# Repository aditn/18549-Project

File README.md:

# PSTR - posture
Project website:
<a href="https://www.ece.cmu.edu/~ece549/spring17/team15/website/"> PSTR official website </a>
Project video link:
N/A (working on it now)

### This is a CMU 18549 project done by Team 15 with the following Team members:
 -  Benson Zhang (yaxiangz)

 - Adit Namdev (anamdev)

 - Tony Jin (tdjin)

 - Nikhil Nilakantan (nnilakan)

## System components

1. Hardware
    > Maintainers: Adit & Nikil

2. Software
    > Maintainers: Benson & Tony

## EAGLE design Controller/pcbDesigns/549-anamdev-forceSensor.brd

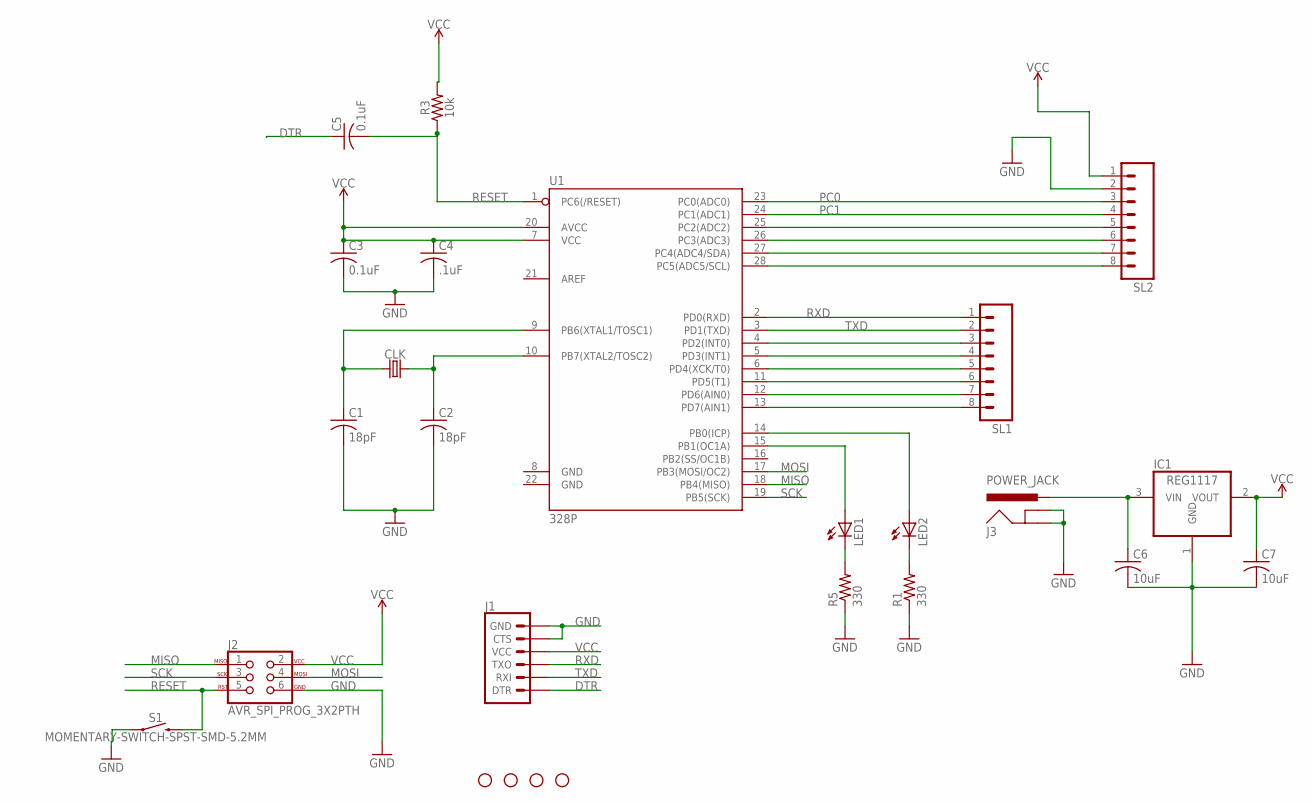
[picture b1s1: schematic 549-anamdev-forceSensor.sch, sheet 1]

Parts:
C1, C2: 18pF; C1206
C3, C5: 0.1uF; C1206
C4: .1uF; C1206
C6, C7: 10uF; C1206
CLK: CRYSTALSMD-HC49UP; HC49UP
H1, H2, H3, H4: STAND-OFF
IC1: REG1117; SOT223
J1: 6_PIN_SERIAL_TARGET; 1X06
J2: AVR_SPI_PROG_3X2PTH; 2X3
J3: POWER_JACK; POWER_JACK_PTH
LED1, LED2: LED1206; LED-1206
R1, R5: 330; R1206
R3: 10k; 1206
S1: MOMENTARY-SWITCH-SPST-SMD-5.2MM; TACTILE_SWITCH_SMD_5.2MM
SL1, SL2: M08; 08P
U1: 328P; DIP28

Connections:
DTR: C5.1, J1.1 (DTR)
GND: C1.2, C2.2, C3.2, C4.2, C6.2, C7.2, IC1.1 (GND), J1.5 (CTS), J1.6 (GND), J2.6, J3.GND, J3.GNDBREAK, R1.1, R5.1, S1.1, SL2.2; also elsewhere on the board
MISO: J2.1, U1.18 (PB4(MISO))
MOSI: J2.4, U1.17 (PB3(MOSI/OC2))
unnamed: LED2.A, U1.14 (PB0(ICP))
unnamed: LED1.C, R5.2
unnamed: LED1.A, U1.15 (PB1(OC1A))
unnamed: LED2.C, R1.2
unnamed: C6.1, IC1.3 (VIN), J3.PWR
unnamed: SL2.6, U1.26 (PC3(ADC3))
unnamed: SL1.5, U1.6 (PD4(XCK/T0))
unnamed: SL1.6, U1.11 (PD5(T1))
unnamed: SL1.7, U1.12 (PD6(AIN0))
unnamed: SL1.8, U1.13 (PD7(AIN1))
unnamed: SL1.3, U1.4 (PD2(INT0))
unnamed: SL1.4, U1.5 (PD3(INT1))
unnamed: C1.1, CLK.1, U1.9 (PB6(XTAL1/TOSC1))
unnamed: C2.1, CLK.2, U1.10 (PB7(XTAL2/TOSC2))
PC0: SL2.3, U1.23 (PC0(ADC0)); also elsewhere on the board
PC1: SL2.4, U1.24 (PC1(ADC1)); also elsewhere on the board
PC2: SL2.5, U1.25 (PC2(ADC2))
RESET: C5.2, J2.5, R3.1, S1.3 (2), U1.1 (PC6(/RESET))
RXD: J1.3 (TXO), SL1.1, U1.2 (PD0(RXD))
SCK: J2.3, U1.19 (PB5(SCK)); also elsewhere on the board
SCL: SL2.8, U1.28 (PC5(ADC5/SCL))
SDA: SL2.7, U1.27 (PC4(ADC4/SDA))
TXD: J1.2 (RXI), SL1.2, U1.3 (PD1(TXD))
VCC: C3.1, C4.1, C7.1, IC1.2 (VOUT), J1.4 (VCC), J2.2, R3.2, SL2.1, U1.7 (VCC), U1.20 (AVCC); also elsewhere on the board

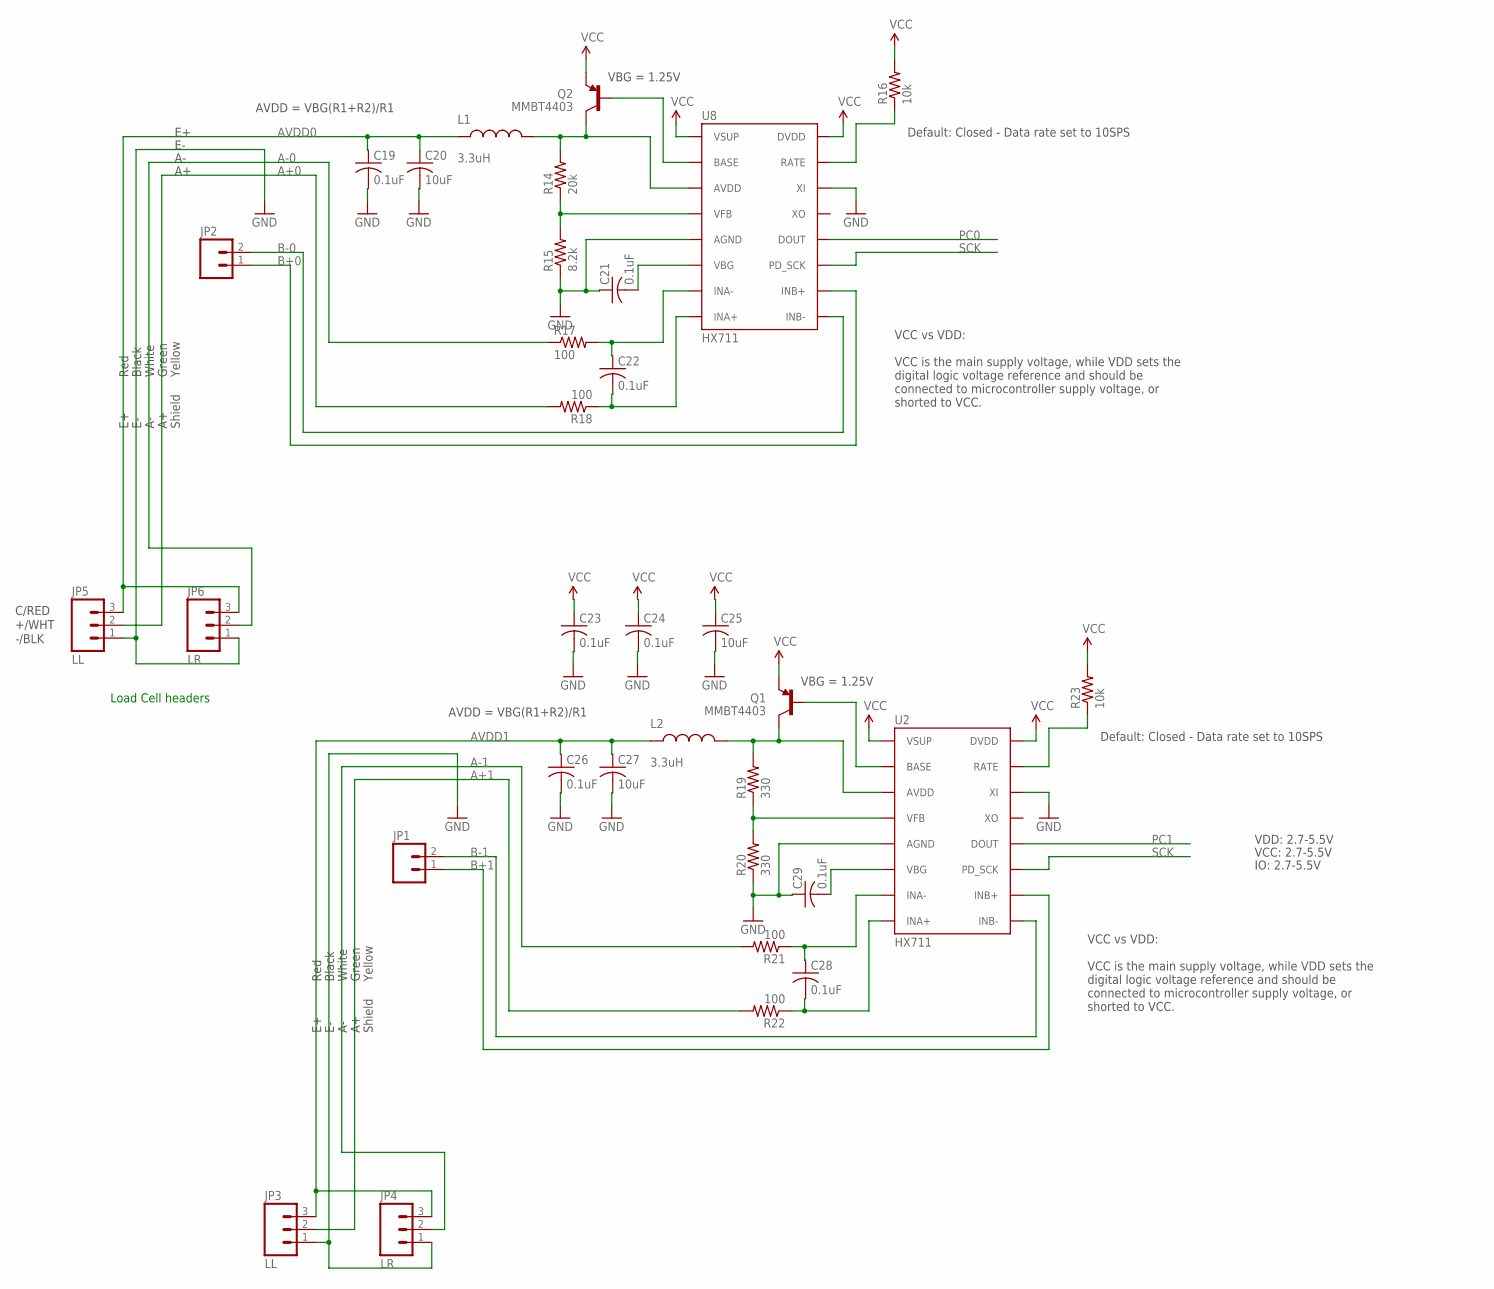
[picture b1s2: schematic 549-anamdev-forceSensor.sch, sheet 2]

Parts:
C19, C21, C22, C23, C24, C26, C28, C29: 0.1uF; C1206
C20, C25, C27: 10uF; C1206
JP1, JP2: M02PTH; 1X02
JP3, JP5: LL; 1X03
JP4, JP6: LR; 1X03
L1, L2: 3.3uH; 0805
Q1, Q2: MMBT4403; SOT23-3
R14: 20k; R1206
R15: 8.2k; R1206
R16, R23: 10k; R1206
R17, R18, R21, R22: 100; R1206
R19, R20: 330; R1206
U2, U8: HX711; SO16

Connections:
A+0: JP5.2, R18.2
A+1: JP3.2, R22.2
A-0: JP6.2, R17.1
A-1: JP4.2, R21.2
AVDD0: C19.1, C20.1, JP5.3, JP6.3, L1.1
AVDD1: C26.1, C27.1, JP3.3, JP4.3, L2.1
B+0: JP2.1, U8.10 (INB+)
B+1: JP1.1, U2.10 (INB+)
B-0: JP2.2, U8.9 (INB-)
B-1: JP1.2, U2.9 (INB-)
GND: C19.2, C20.2, C21.1, C23.2, C24.2, C25.2, C26.2, C27.2, C29.1, JP3.1, JP4.1, JP5.1, JP6.1, R15.1, R20.1, U2.5 (AGND), U2.14 (XI), U8.5 (AGND), U8.14 (XI); also elsewhere on the board
unnamed: Q2.1 (B), U8.2 (BASE)
unnamed: R14.1, R15.2, U8.4 (VFB)
unnamed: C21.2, U8.6 (VBG)
unnamed: L1.2, Q2.3 (C), R14.2, U8.3 (AVDD)
unnamed: R16.1, U8.15 (RATE)
unnamed: C22.1, R17.2, U8.7 (INA-)
unnamed: C22.2, R18.1, U8.8 (INA+)
unnamed: Q1.1 (B), U2.2 (BASE)
unnamed: R19.1, R20.2, U2.4 (VFB)
unnamed: C29.2, U2.6 (VBG)
unnamed: L2.2, Q1.3 (C), R19.2, U2.3 (AVDD)
unnamed: R23.1, U2.15 (RATE)
unnamed: C28.1, R21.1, U2.7 (INA-)
unnamed: C28.2, R22.1, U2.8 (INA+)
PC0: U8.12 (DOUT); also elsewhere on the board
PC1: U2.12 (DOUT); also elsewhere on the board
SCK: U2.11 (PD_SCK), U8.11 (PD_SCK); also elsewhere on the board
VCC: C23.1, C24.1, C25.1, Q1.2 (E), Q2.2 (E), R16.2, R23.2, U2.1 (VSUP), U2.16 (DVDD), U8.1 (VSUP), U8.16 (DVDD); also elsewhere on the board

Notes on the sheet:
VBG = 1.25V
AVDD = VBG(R1+R2)/R1
Default: Closed - Data rate set to 10SPS
VCC vs VDD: VCC is the main supply voltage, while VDD sets the digital logic voltage reference and should be connected to microcontroller supply voltage, or shorted to VCC.
Red
Black
White
Green
-/BLK
+/WHT
C/RED
Shield
Yellow
Load Cell headers
VCC: 2.7-5.5V
IO: 2.7-5.5V
VDD: 2.7-5.5V

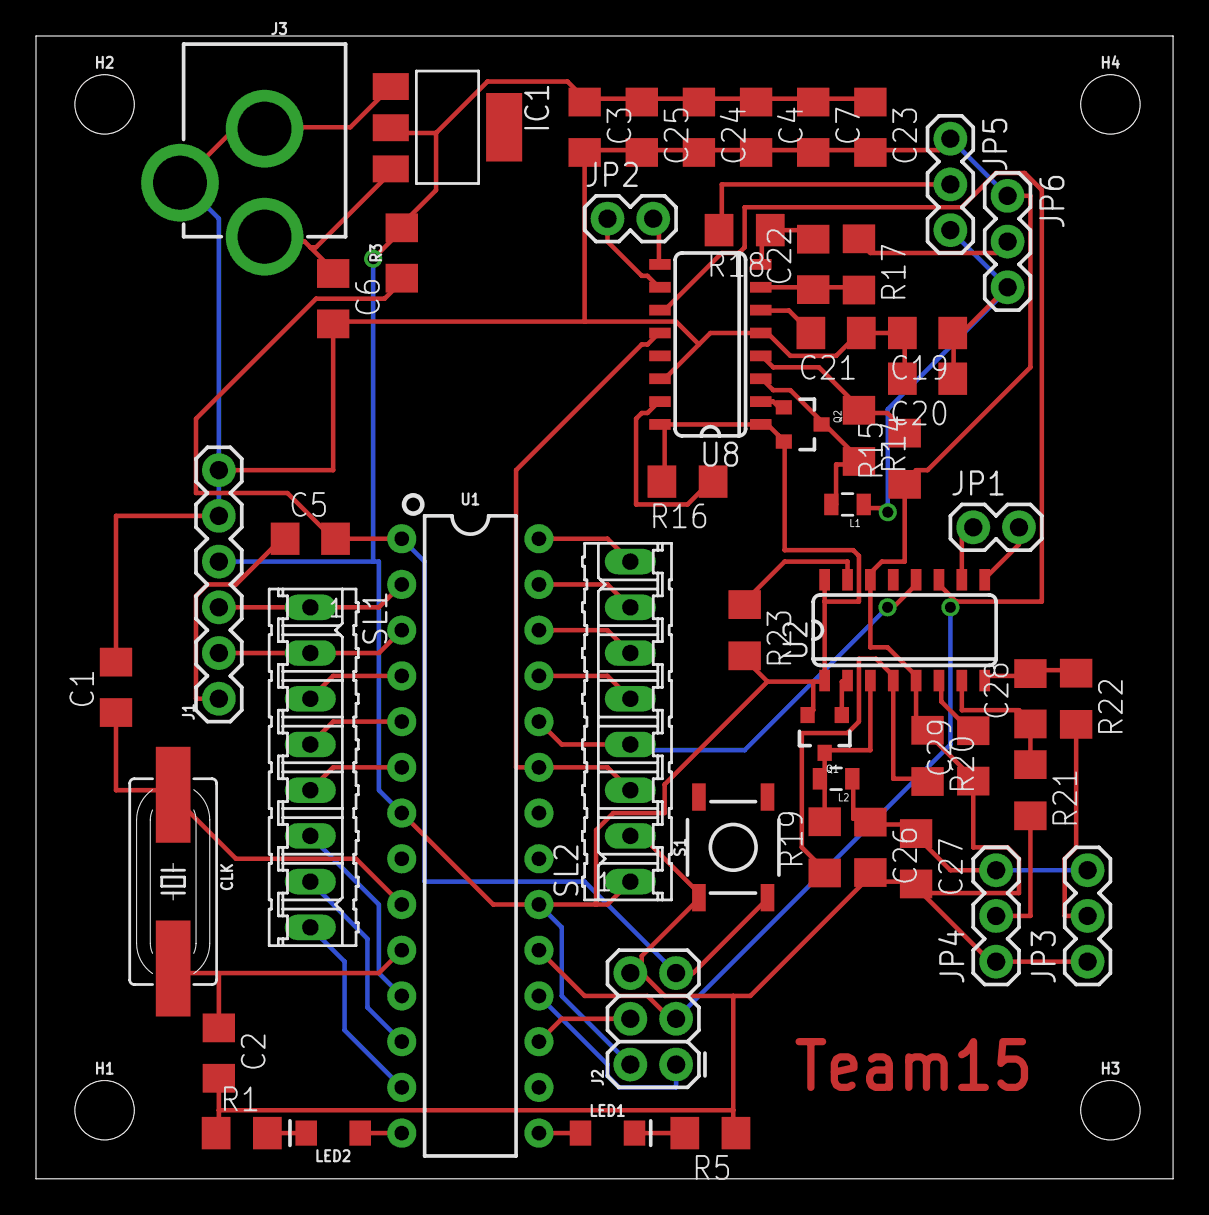
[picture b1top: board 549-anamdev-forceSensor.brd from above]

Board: 2 copper layers, 63.2 x 63.5 mm, 58 parts (0 on the bottom side), 52 nets.

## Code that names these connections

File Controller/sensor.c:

/*
  sensor.c
*/

#include "sensor.h"
#include <avr/interrupt.h>
#include <stdio.h>


void sensor_init(){

  /************ LOAD CELL MCU **************/
  //DDRC |= (1<<PC0); // Set PC0(clk) as an output pin
  //DDRC &= ~(1<<PC1); // Set PC1(data) as input pin

  //SENSORS[SENSOR0].CLK = PC0;
  //SENSORS[SENSOR0].DATA = PC1;
  //SENSORS[SENSOR0].DIR_REG = &DDRC;
  //SENSORS[SENSOR0].PORT_OUTPUT_REG = &PORTC;
  //SENSORS[SENSOR0].PORT_INPUT_REG = &PINC;
  //SENSORS[SENSOR0].CALIB_FACTOR = -12000;

  /* Initializing second sensor */
  //DDRC |= (1<<PC2); // Set P(clk) as an output pin
  //DDRC &= ~(1<<PC3); // Set PC3(data) as input pin

  //SENSORS[SENSOR1].CLK = PC2;
  //SENSORS[SENSOR1].DATA = PC3;
  //SENSORS[SENSOR1].DIR_REG = &DDRC;
  //SENSORS[SENSOR1].PORT_OUTPUT_REG = &PORTC;
  //SENSORS[SENSOR1].PORT_INPUT_REG = &PINC;
  //SENSORS[SENSOR1].CALIB_FACTOR = -11000;
  /* Initializing second sensor */


  /* Initializing THIRD PORTD sensor */
  //DDRD |= (1<<PD7); // Set PD7(clk) as an output pin
  //DDRD &= ~(1<<PD6); // Set PD6(data) as input pin

  //SENSORS[SENSOR2].CLK = PD7;
  //SENSORS[SENSOR2].DATA = PD6;
  //SENSORS[SENSOR2].DIR_REG = &DDRD;
  //SENSORS[SENSOR2].PORT_OUTPUT_REG = &PORTD;
  //SENSORS[SENSOR2].PORT_INPUT_REG = &PIND;
  //SENSORS[SENSOR2].CALIB_FACTOR = -11000;
  /* Initializing THIRD PORTD sensor */

  /* Initializing FOURTH PORTB sensor */
  //DDRB |= (1<<PB5); // Set PB5(clk) as an output pin
  //DDRB &= ~(1<<PB4); // Set PB4(data) as input pin

  //SENSORS[SENSOR3].CLK = PB5;
  //SENSORS[SENSOR3].DATA = PB4;
  //SENSORS[SENSOR3].DIR_REG = &DDRB;
  //SENSORS[SENSOR3].PORT_OUTPUT_REG = &PORTB;
  //SENSORS[SENSOR3].PORT_INPUT_REG = &PINB;
  //SENSORS[SENSOR3].CALIB_FACTOR = -11000;
  /* Initializing THIRD PORTD sensor */
  /************ LOAD CELL MCU **************/


  /**************** FSR MCU ****************/
  DDRC &= (~_BV(PC2) | ~_BV(PC1) | ~_BV(PC0)); // Set ADC pins PC(2-0) as input pins
  /**************** FSR MCU ****************/
}

uint16_t adc_read(uint8_t adcx) {
  /* adcx is the analog pin we want to use.  ADMUX's first few bits are
   * the binary representations of the numbers of the pins so we can
   * just 'OR' the pin's number with ADMUX to select that pin.
   * We first zero the four bits by setting ADMUX equal to its higher
   * four bits. */

  ADMUX &=  0xf0;
  ADMUX |=  adcx;

  /* This starts the conversion. */
  ADCSRA |= _BV(ADSC);

  /* This is an idle loop that just wait around until the conversion
   * is finished.  It constantly checks ADCSRA's ADSC bit, which we just
   * set above, to see if it is still set.  This bit is automatically
   * reset (zeroed) when the conversion is ready so if we do this in
   * a loop the loop will just go until the conversion is ready. */
  while (!( ADCSRA & _BV(ADIF)) );

  uint16_t adcV = ADC;
  ADCSRA |= _BV(ADIF);
  //printf("adcV:%d\n\r",adcV);


  /* Finally, we return the converted value to the calling function. */
  return adcV;
}

void adc_init(){
   // disable interrupts
   //cli();

   // Set the ADC prescaler to 128 (i.e., 16MHz/128 = 125KHz)
   ADCSRA |= ( 1 << ADPS2 ) | ( 1 << ADPS1 ) | ( 1 << ADPS0 );

   // Set the voltage reference from AVcc (i.e., 5V).
   ADMUX |= ( 1 << REFS0 );

   // Turn on the ADC.
   ADCSRA |= ( 1 << ADEN );

   // Do the initial conversion (i.e., the slowest conversion)
   // to ensure that everything is up and running.
   //ADCSRA |= ( 1 << ADSC );
  
   //enable interrupts
   //sei();
}

uint32_t read_avg_force(uint8_t sensor_id, uint8_t times){
  uint32_t avg=0;
  uint8_t i;
  for (i=0;i<times;i++){
     avg+=ReadCount(sensor_id);
  }
  avg/=times;
  return avg;
} 

void tare(){
  uint8_t sensor_id=0;

  for (sensor_id=0; sensor_id < NUMBER_OF_SENSORS; sensor_id++) {
    SENSORS[sensor_id].CALIB_OFFSET = 0;
    SENSORS[sensor_id].CALIB_OFFSET = read_avg_force(sensor_id, 15);
    printf("taring sensor%d:%lu\n\r",sensor_id, SENSORS[sensor_id].CALIB_OFFSET);
  }
}

float read_calibrated_value(uint8_t sensor_id){
  uint32_t avg;
  int32_t avg_offset;
 
  float calib_val=0;
  avg = read_avg_force(sensor_id, 2);
  avg_offset = ((int32_t)avg-SENSORS[sensor_id].CALIB_OFFSET);
  calib_val = (float)avg_offset/SENSORS[sensor_id].CALIB_FACTOR;
 
  return(calib_val);
}

uint32_t ReadCount(uint8_t sensor_id){
  uint32_t Count;
  uint8_t i;

  uint8_t clk = SENSORS[sensor_id].CLK;
  uint8_t data = SENSORS[sensor_id].DATA;
  volatile uint8_t *output_reg = SENSORS[sensor_id].PORT_OUTPUT_REG;
  volatile uint8_t *input_reg = SENSORS[sensor_id].PORT_INPUT_REG;

  *output_reg &= ~_BV(clk);
  *output_reg |= _BV(data);

  Count=0;

  while(*input_reg & _BV(data)); 
  for (i=0;i<24;i++){
    *output_reg |= _BV(clk);
    Count=Count<<1;
    *output_reg &= ~_BV(clk);
    if(*input_reg & _BV(data)) Count++;
  }
  
  *output_reg |= _BV(clk);
  Count=Count^0x800000;
  *output_reg &= ~_BV(clk);

  return(Count);
} 

void collectforceData(float* data){
  data[SENSOR0] = read_calibrated_value(SENSOR0);

  data[SENSOR1] = read_calibrated_value(SENSOR1);

  data[SENSOR2] = read_calibrated_value(SENSOR2);

  data[SENSOR3] = read_calibrated_value(SENSOR3);
}

void read_FSR(float* data) {
  data[SENSOR0] = adc_read(PC0);
  data[SENSOR1] = adc_read(PC1);
  data[SENSOR2] = adc_read(PC2);
}

void LED_green_on(){
  DDRC |= (1<<PC0);

  // set PC0 and PC1 to logic 1
  PORTC |= (1<<PC0);
}
void LED_green_off(){
  PORTC &= ~(1<<PC0);
}
void LED_red_on(){
  DDRC |= (1<<PC1);

  // set PC1 to logic 1
  PORTC |= (1<<PC1);
}
void LED_red_off(){
  PORTC &= ~(1<<PC1);
}

void LED_both_on(){
  // set Pins PC0,PC1 as outputs
  //DDRC = 0;
  DDRC |= (1<<PC0) | (1<<PC1);

  // set PC0 and PC1 to logic 1
  PORTC |= (1<<PC0) | (1<<PC1);
}

void LED_both_off(){
  // set Pins PC0,PC1 as outputs
  //DDRC = 0;
  //DDRC |= (1<<PC0) | (1<<PC1);

  // set PC0 and PC1 to logic 1
  PORTC &= ~((1<<PC0) | (1<<PC1));
}

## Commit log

2016-11-26 updated post_serial script to wait 3 seconds before sending first data request. Need to add POST request to server.
2016-11-26 reorganized Rpi folder
2017-03-05 started Project Repo
2017-03-08 finished lab 3
2017-03-21 added first iteration of force sensor board for a single force sensor
2017-03-27 sc webserver v1
2017-03-28 sample json in readme
2017-03-28 rpi python script for POST request
2017-03-29 connected to AWS mySQL database; POST request POSTs to database
2017-03-29 added multiple amplifiers for force sensor
2017-03-29 checking out to old branch
2017-04-01 sc user website
2017-04-02 Added basic framework
2017-04-03 Added a README.md
2017-04-06 testing serial communication of force values
2017-04-07 updated pcb boards
2017-04-07 cleaned up code and have functioning communication over uart
2017-04-07 Load sensor amp test before calibration
2017-04-09 post_serial takes serial data from microcontroller and posts to web server (untested)
2017-04-10 changed format of data being written to serial port
2017-04-10 reading data on RPi
2017-04-10 changed port to ser
2017-04-10 fixed issue for string parsing
2017-04-10 added post request for serial
2017-04-12 I2C Skeleton for Pi and ATMega, need to flash onto ATMega
2017-04-13 fixed issues with pcb
2017-04-13 added i2c files to Makefile
2017-04-13 Moved I2C library to working Controller directory for debugging
2017-04-13 adding sensor.h
2017-04-17 Updated server.js : disabled sql connect
2017-04-17 New idea for the chair model
2017-04-24 Added Rpi i2c test
2017-04-24 Rpi receiving strings from atmega
2017-04-24 Added slava data parsing and json post functionality to RPi master
2017-04-24 Cleaned up Rpi I2C coe to receive real force data
2017-04-25 initial code for checking posture
2017-04-25 DB should now work for all IPs and not throw err
2017-04-25 I2C Working on multiple devices for one byte
2017-04-26 ATMega sending strings over I2C
2017-04-26 Added chair and camera
2017-04-26 Added chair sensor points and simulated data
2017-04-27 Commented main.c and included space to implement force sensor read
2017-04-27 uploaded new server. now can GET fake sensor data. also added sample python get request format
2017-04-30 checking out previously working branch
2017-04-30 checking out
2017-04-30 mcu code nearly finished
2017-05-01 GET request to server returns all data or last N rows
2017-05-01 refined example POST and GET requests and added a README on request formats
2017-05-01 formatting
2017-05-01 fixed sensor1 being inputted as null
2017-05-01 fixed GET number of entries always returns 10 entries
2017-05-01 added more graceful error handling
2017-05-01 fixed rpi post, i2c_comm string format
2017-05-01 Finished chair model and such
2017-05-01 Fixed some simple bug
2017-05-01 finished mcu side, need to add more pins for more ADCs
2017-05-01 Reading force sensor data over I2C
2017-05-01 added commenting to posture.py and refined posture score calculations
2017-05-02 Added code for multiple sensor reading on one board
2017-05-02 Changed sensor storage to array of structs
2017-05-02 Changed calibration factor definitions
2017-05-02 Changed defines.h
2017-05-02 added hex files to .gitignore
2017-05-02 this branch is ready to merge into master
2017-05-03 Fixed multiple sensor feedback
2017-05-04 Getting feedback from all sensors
2017-05-04 Four sensor functionality
2017-05-05 changed db schema and server to accomodate force pad sensors. added posture checking to server side. updated example GET and POST and README
2017-05-05 changed POST request keys to fsrX
2017-05-05 posture algo updated
2017-05-05 pulling..
2017-05-05 Added code for second MCU with FSR
2017-05-05 added backend server support for different users
2017-05-06 Added starter page for interactive website
2017-05-06 correctly calculating data from FSRs. Need to test I2C with Rpi
2017-05-06 fixed i2c_comm
2017-05-06 added loop to I2C code to query multiple MCUs
2017-05-06 fixed popping error
2017-05-08 reduced number of times load cell data is taken to improve latency
2017-05-08 removed print statements
2017-05-08 reduced sleep time
2017-05-08 tweaked posture algorithm weight percentages. fixed negative pos score error
2017-05-09 added script to continuously query db
2017-05-09 fixed error in query script
2017-05-09 catch exceptions for requests and try maximum 3 times
2017-05-10 added calibration onto the pi
2017-05-10 moved server response to beginning of POST request to speed up post request for Rpi
2017-05-10 added code for speaker
2017-05-10 data collection script and .json data files
2017-05-11 added script to collect stats of different postures
2017-05-11 merging
2017-05-11 added posture status
2017-05-11 fixed incorrect lowercase strings
2017-05-11 Updated old website
2017-05-11 fixed typo in status_string
2017-05-12 Last update, almost
2017-05-12 updated posture algo
2017-05-12 sm_server_v21 update
2017-05-12 updated algo for leaning too far forward
2017-05-12 Fixed a tiny bug
2017-05-13 tweaked posture parameters

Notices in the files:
parts and their libraries:
SparkFun-Clocks: Licensing: Creative Commons ShareAlike 4.0 International - https://creativecommons.org/licenses/by-sa/4.0
SparkFun-Aesthetics: Licensing: CC v3.0 Share-Alike You are welcome to use this library for commercial purposes.
